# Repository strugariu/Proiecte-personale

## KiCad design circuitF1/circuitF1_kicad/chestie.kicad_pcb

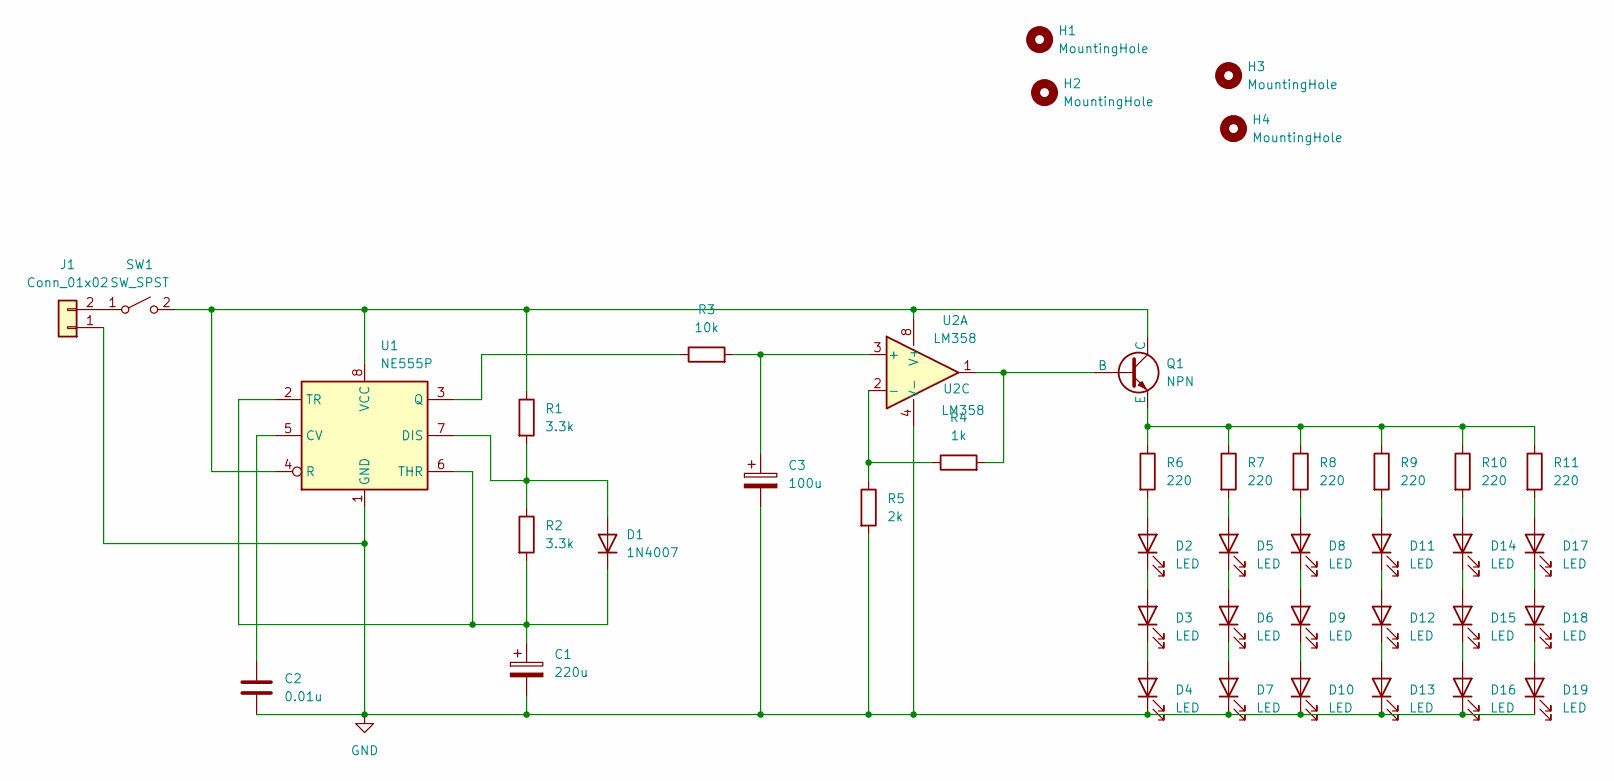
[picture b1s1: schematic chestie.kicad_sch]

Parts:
C1: 220u; CP_Radial_D6.3mm_P2.50mm
C2: 0.01u; C_Disc_D7.5mm_W4.4mm_P5.00mm
C3: 100u; CP_Radial_D6.3mm_P2.50mm
D1: 1N4007; D_DO-41_SOD81_P10.16mm_Horizontal
D2, D3, D4, D5, D6, D7, D8, D9, D10, D11, D12, D13, D14, D15, D16, D17, D18, D19: LED; LED_D5.0mm
H1, H2, H3, H4: MountingHole; MountingHole_3.2mm_M3
J1: Conn_01x02; SolderWire-0.75sqmm_1x02_P7mm_D1.25mm_OD3.5mm
Q1: NPN; TO-92_Inline
R1, R2: 3.3k; R_Axial_DIN0207_L6.3mm_D2.5mm_P7.62mm_Horizontal
R3: 10k; R_Axial_DIN0207_L6.3mm_D2.5mm_P7.62mm_Horizontal
R4: 1k; R_Axial_DIN0207_L6.3mm_D2.5mm_P7.62mm_Horizontal
R5: 2k; R_Axial_DIN0207_L6.3mm_D2.5mm_P7.62mm_Horizontal
R6, R7, R8, R9, R10, R11: 220; R_Axial_DIN0207_L6.3mm_D2.5mm_P7.62mm_Horizontal
SW1: SW_SPST; SW_Slide_SPDT_Straight_CK_OS102011MS2Q
U1: NE555P; DIP-8_W7.62mm
U2: LM358; DIP-8_W7.62mm

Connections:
GND: C1.2, C2.2, C3.2, D4.1 (K), D7.1 (K), D10.1 (K), D13.1 (K), D16.1 (K), D19.1 (K), J1.1, R5.2, U1.1 (GND), U2.4 (V-)
unnamed: D1.2 (A), R1.2, R2.1, U1.7 (DIS)
unnamed: C1.1, D1.1 (K), R2.2, U1.2 (TR), U1.6 (THR)
unnamed: D2.2 (A), R6.2
unnamed: D2.1 (K), D3.2 (A)
unnamed: D3.1 (K), D4.2 (A)
unnamed: D5.2 (A), R7.2
unnamed: D5.1 (K), D6.2 (A)
unnamed: D6.1 (K), D7.2 (A)
unnamed: D8.2 (A), R8.2
unnamed: D8.1 (K), D9.2 (A)
unnamed: D9.1 (K), D10.2 (A)
unnamed: D11.2 (A), R9.2
unnamed: D11.1 (K), D12.2 (A)
unnamed: D12.1 (K), D13.2 (A)
unnamed: D14.2 (A), R10.2
unnamed: D14.1 (K), D15.2 (A)
unnamed: D15.1 (K), D16.2 (A)
unnamed: D17.2 (A), R11.2
unnamed: D17.1 (K), D18.2 (A)
unnamed: D18.1 (K), D19.2 (A)
unnamed: J1.2, SW1.1 (A)
unnamed: Q1.2 (B), R4.2, U2.1
unnamed: Q1.1 (C), R1.1, SW1.2 (B), U1.4 (R), U1.8 (VCC), U2.8 (V+)
unnamed: Q1.3 (E), R6.1, R7.1, R8.1, R9.1, R10.1, R11.1
unnamed: C2.1, U1.5 (CV)
unnamed: R3.1, U1.3 (Q)
unnamed: C3.1, R3.2, U2.3 (+)
unnamed: R4.1, R5.1, U2.2 (-)

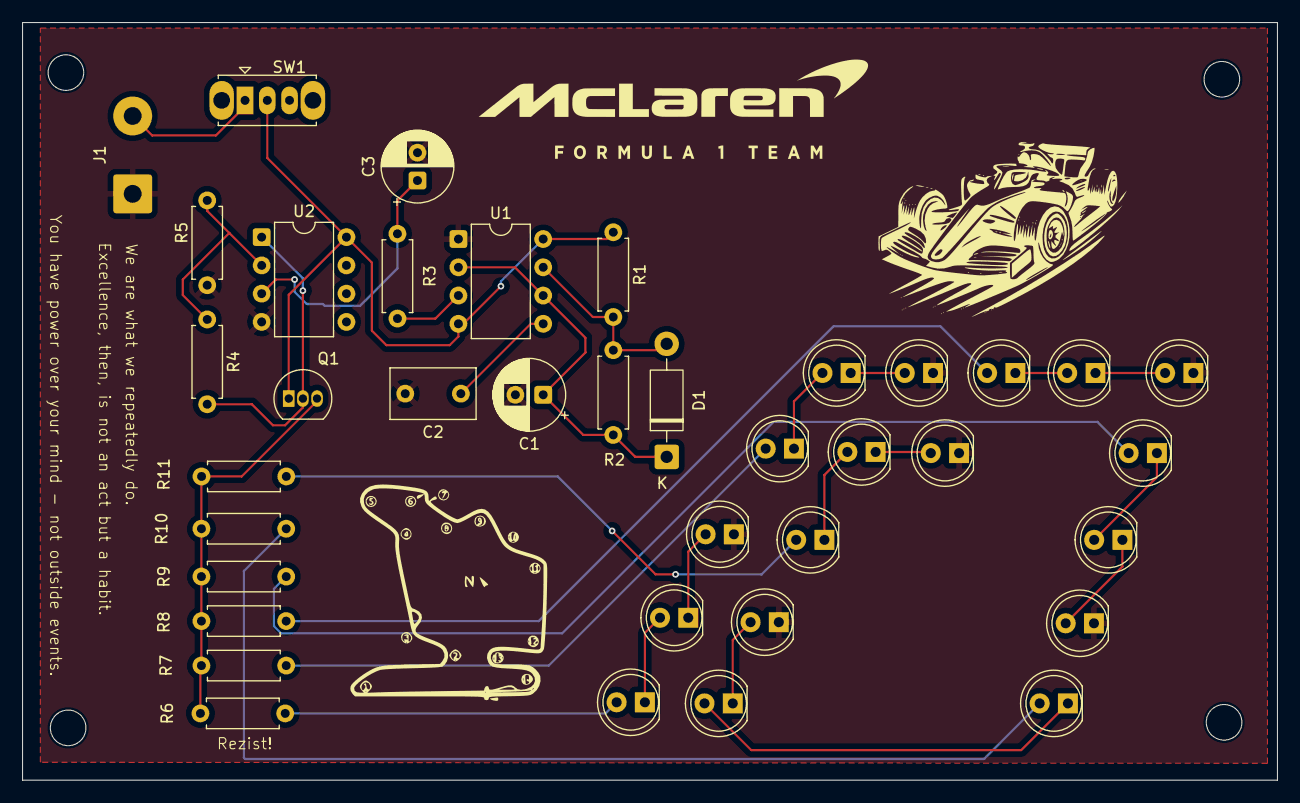
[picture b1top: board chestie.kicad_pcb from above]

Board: 2 copper layers, 112.8 x 68.1 mm, 42 parts (0 on the bottom side), 29 nets.

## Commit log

2025-11-04 Proiecte
